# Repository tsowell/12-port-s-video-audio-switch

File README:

KiCad design, AVR code, and misc CAD files for a 12-port S-Video/audio
switch with VFD display, described in detail here:

https://blog.ldtlb.com/2021/03/25/12-port-s-video-audio-switch.html

The design in the KiCad files has multiple flaws.  Most importantly, the
terminating resistors for the luminance and chroma inputs were omitted, and the
+5VD voltage regualt can become quite hot without a large heatsink.  These are
explained in more detail in the post above.

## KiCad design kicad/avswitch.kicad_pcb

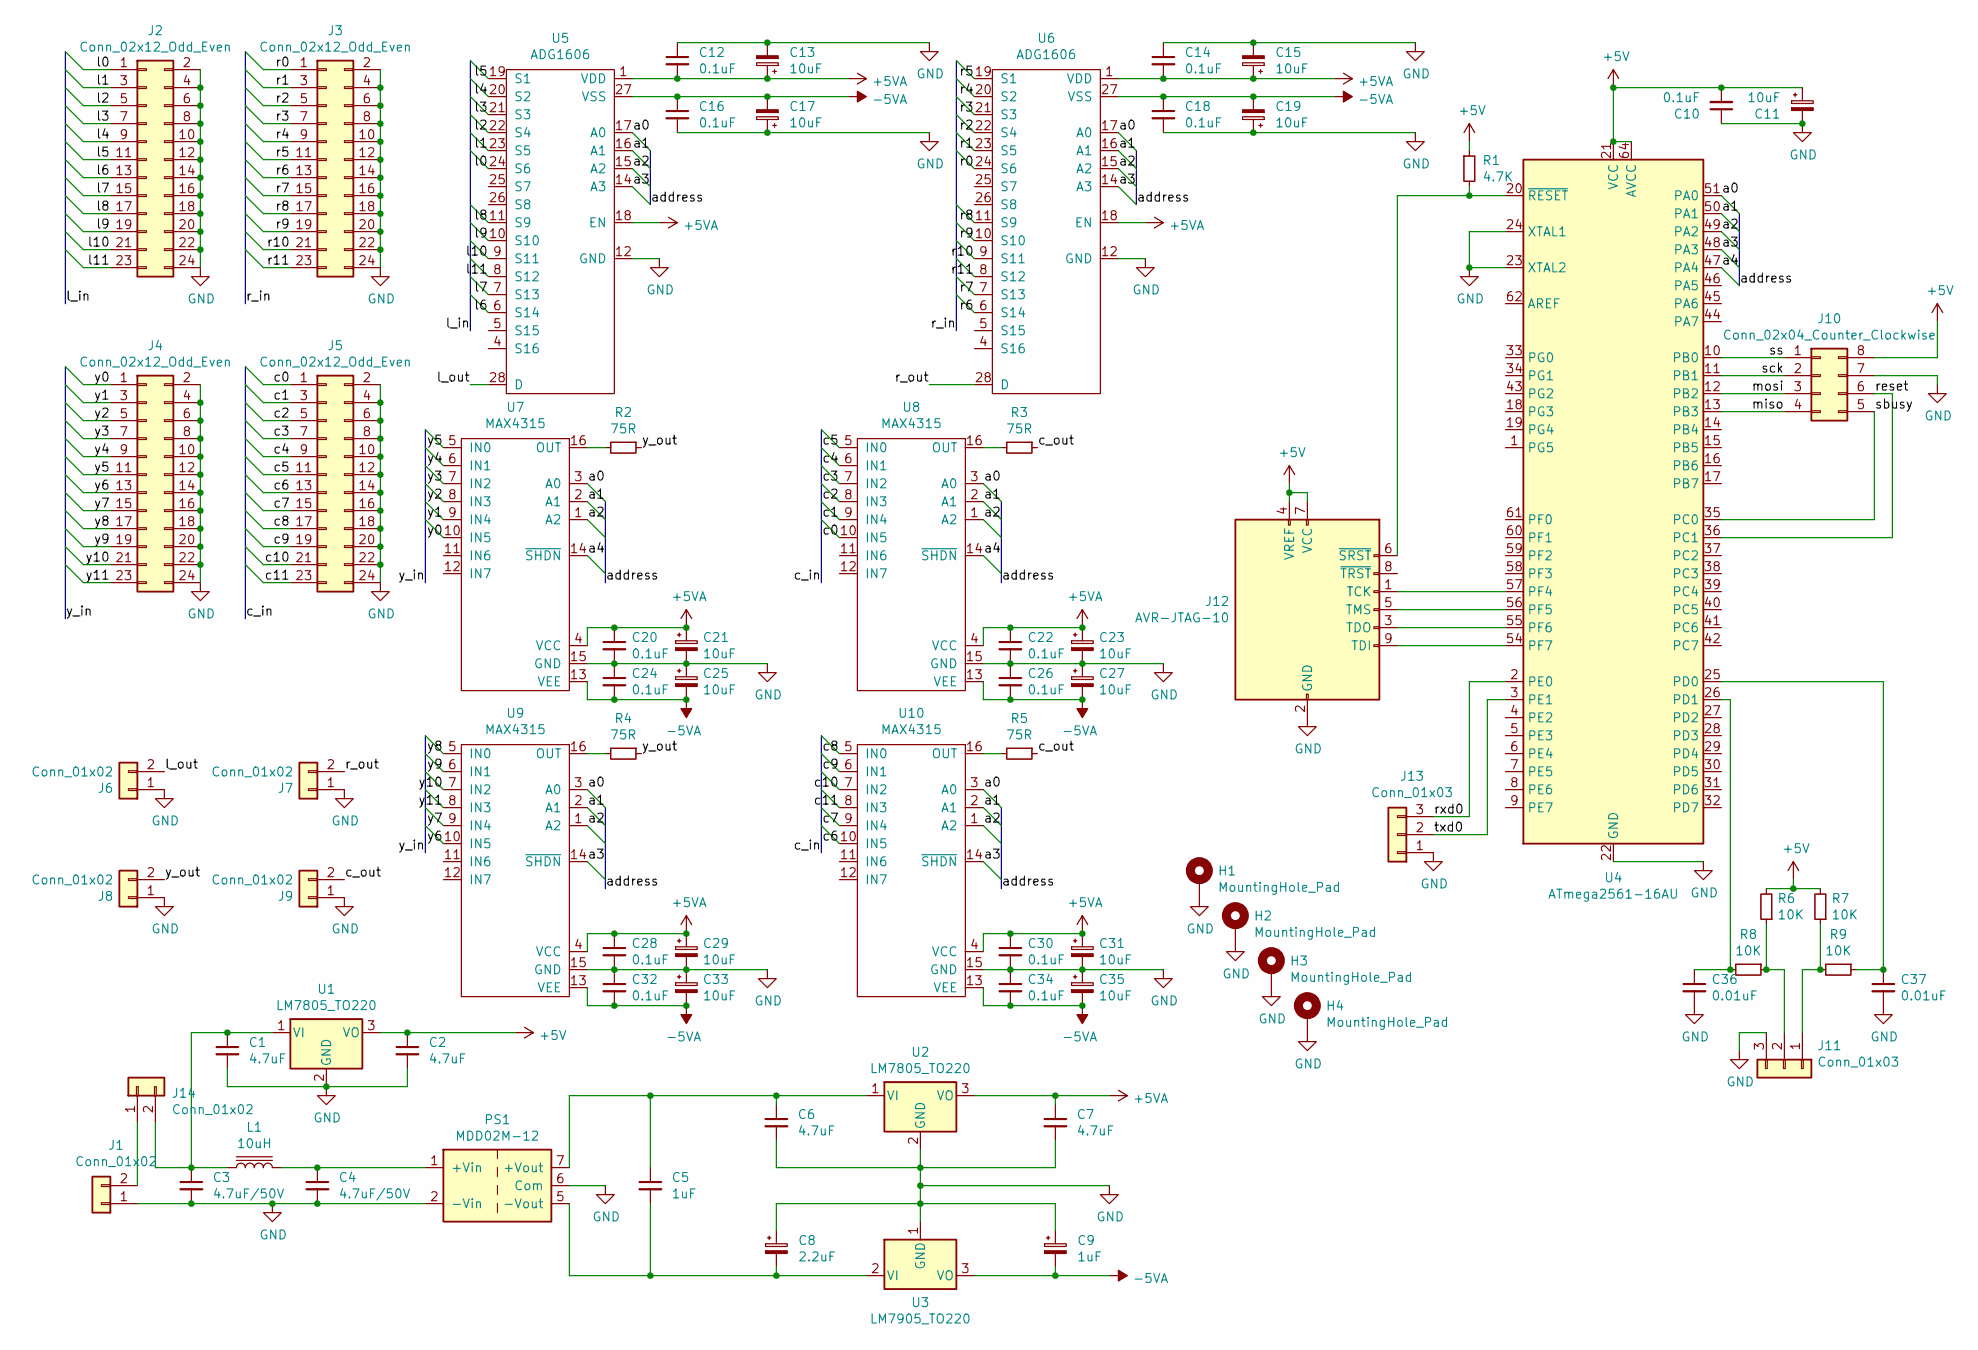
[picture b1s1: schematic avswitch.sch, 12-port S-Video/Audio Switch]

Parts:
C1, C2, C6, C7: 4.7uF; C_1206_3216Metric_Pad1.42x1.75mm_HandSolder; Part 399-3524-1-ND
C3, C4: 4.7uF/50V; C_1206_3216Metric_Pad1.42x1.75mm_HandSolder; Part 399-11685-1-ND
C5: 1uF; C_1206_3216Metric_Pad1.42x1.75mm_HandSolder; Part 399-1254-1-ND
C8: 2.2uF; CP_EIA-3216-18_Kemet-A_Pad1.58x1.35mm_HandSolder; Part 399-3691-1-ND
C9: 1uF; CP_EIA-3216-18_Kemet-A_Pad1.58x1.35mm_HandSolder; Part 399-3678-1-ND
C10, C12, C14, C16, C18, C20, C22, C24, C26, C28, C30, C32, C34: 0.1uF; C_1206_3216Metric_Pad1.42x1.75mm_HandSolder; Part 399-9305-1-ND
C11, C13, C15, C17, C19, C21, C23, C25, C27, C29, C31, C33, C35: 10uF; CP_Elec_4x5.4; Part 493-2173-1-ND
C36, C37: 0.01uF; C_1206_3216Metric_Pad1.42x1.75mm_HandSolder; Part 399-14645-1-ND
H1, H2, H3, H4: MountingHole_Pad; MountingHole_3.2mm_M3_Pad_Via
J1, J6, J7, J8, J9, J14: Conn_01x02; Molex_KK-254_AE-6410-02A_1x02_P2.54mm_Vertical; Part WM2700-ND
J2, J3, J4, J5: Conn_02x12_Odd_Even; PinHeader_2x12_P2.54mm_Vertical; Part ED10525-ND
J10: Conn_02x04_Counter_Clockwise; PinHeader_2x04_P2.54mm_Vertical; Part 732-5395-ND
J11: Conn_01x03; Molex_KK-254_AE-6410-03A_1x03_P2.54mm_Vertical; Part WM2701-ND
J12: AVR-JTAG-10; PinHeader_2x05_P1.27mm_Vertical; Part 1175-1627-ND
J13: Conn_01x03; PinHeader_1x03_P2.54mm_Vertical
L1: 10uH; L_1206_3216Metric_Pad1.42x1.75mm_HandSolder; Part 541-2607-6-ND
PS1: MDD02M-12; Part 1866-3383-ND
R1: 4.7K; R_1206_3216Metric_Pad1.42x1.75mm_HandSolder; Part 311-4.7KERCT-ND
R2, R3, R4, R5: 75R; R_1206_3216Metric_Pad1.42x1.75mm_HandSolder; Part 311-75ERCT-ND
R6, R7, R8, R9: 10K; R_1206_3216Metric_Pad1.42x1.75mm_HandSolder; Part 311-10KERCT-ND
U1, U2: LM7805_TO220; TO-220-3_Vertical; Part 296-47192-ND
U3: LM7905_TO220; TO-220-3_Vertical; Part LM7905CTNS/NOPB-ND
U4: ATmega2561-16AU; TQFP-64_14x14mm_P0.8mm; Part ATMEGA2561-16AURCT-ND
U5, U6: ADG1606; TSSOP-28_4.4x9.7mm_P0.65mm; Part ADG1606BRUZ-REEL7CT-ND
U7, U8, U9, U10: MAX4315; SOIC-16_3.9x9.9mm_P1.27mm

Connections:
+5V: C2.1, C10.2, C11.1, J10.8, J12.4 (VREF), J12.7 (VCC), R1.1, R6.2, R7.2, U1.3 (VO), U4.21 (VCC), U4.52 (VCC), U4.64 (AVCC)
+5VA: C7.1, C12.2, C13.1, C14.2, C15.1, C20.1, C21.1, C22.1, C23.1, C28.1, C29.1, C30.1, C31.1, U2.3 (VO), U5.1 (VDD), U5.18 (EN), U6.1 (VDD), U6.18 (EN), U7.4 (VCC), U8.4 (VCC), U9.4 (VCC), U10.4 (VCC)
-5VA: C9.2, C16.1, C17.2, C18.1, C19.2, C24.2, C25.2, C26.2, C27.2, C32.2, C33.2, C34.2, C35.2, U3.3 (VO), U5.27 (VSS), U6.27 (VSS), U7.13 (VEE), U8.13 (VEE), U9.13 (VEE), U10.13 (VEE)
/a0: U4.51 (PA0), U5.17 (A0), U6.17 (A0), U7.3 (A0), U8.3 (A0), U9.3 (A0), U10.3 (A0)
/a1: U4.50 (PA1), U5.16 (A1), U6.16 (A1), U7.2 (A1), U8.2 (A1), U9.2 (A1), U10.2 (A1)
/a2: U4.49 (PA2), U5.15 (A2), U6.15 (A2), U7.1 (A2), U8.1 (A2), U9.1 (A2), U10.1 (A2)
/a3: U4.48 (PA3), U5.14 (A3), U6.14 (A3), U9.14 (~SHDN), U10.14 (~SHDN)
/a4: U4.47 (PA4), U7.14 (~SHDN), U8.14 (~SHDN)
/c0: J5.1, U8.10 (IN5)
/c1: J5.3, U8.9 (IN4)
/c2: J5.5, U8.8 (IN3)
/c3: J5.7, U8.7 (IN2)
/c4: J5.9, U8.6 (IN1)
/c5: J5.11, U8.5 (IN0)
/c6: J5.13, U10.10 (IN5)
/c7: J5.15, U10.9 (IN4)
/c8: J5.17, U10.5 (IN0)
/c9: J5.19, U10.6 (IN1)
/c10: J5.21, U10.7 (IN2)
/c11: J5.23, U10.8 (IN3)
/c_out: J9.2, R3.1, R5.1
/l0: J2.1, U5.24 (S6)
/l1: J2.3, U5.23 (S5)
/l2: J2.5, U5.22 (S4)
/l3: J2.7, U5.21 (S3)
/l4: J2.9, U5.20 (S2)
/l5: J2.11, U5.19 (S1)
/l6: J2.13, U5.6 (S14)
/l7: J2.15, U5.7 (S13)
/l8: J2.17, U5.11 (S9)
/l9: J2.19, U5.10 (S10)
/l10: J2.21, U5.9 (S11)
/l11: J2.23, U5.8 (S12)
/l_out: J6.2, U5.28 (D)
/miso: J10.4, U4.13 (PB3)
/mosi: J10.3, U4.12 (PB2)
/r0: J3.1, U6.24 (S6)
/r1: J3.3, U6.23 (S5)
/r2: J3.5, U6.22 (S4)
/r3: J3.7, U6.21 (S3)
/r4: J3.9, U6.20 (S2)
/r5: J3.11, U6.19 (S1)
/r6: J3.13, U6.6 (S14)
/r7: J3.15, U6.7 (S13)
/r8: J3.17, U6.11 (S9)
/r9: J3.19, U6.10 (S10)
/r10: J3.21, U6.9 (S11)
/r11: J3.23, U6.8 (S12)
/r_out: J7.2, U6.28 (D)
/reset: J10.6, U4.36 (PC1)
/rxd0: J13.3, U4.2 (PE0)
/sbusy: J10.5, U4.35 (PC0)
/sck: J10.2, U4.11 (PB1)
/ss: J10.1, U4.10 (PB0)
/txd0: J13.2, U4.3 (PE1)
/y0: J4.1, U7.10 (IN5)
/y1: J4.3, U7.9 (IN4)
/y2: J4.5, U7.8 (IN3)
/y3: J4.7, U7.7 (IN2)
/y4: J4.9, U7.6 (IN1)
/y5: J4.11, U7.5 (IN0)
/y6: J4.13, U9.10 (IN5)
/y7: J4.15, U9.9 (IN4)
/y8: J4.17, U9.5 (IN0)
/y9: J4.19, U9.6 (IN1)
/y10: J4.21, U9.7 (IN2)
/y11: J4.23, U9.8 (IN3)
/y_out: J8.2, R2.1, R4.1
GND: C1.2, C2.2, C3.2, C4.2, C6.2, C7.2, C8.1, C9.1, C10.1, C11.2, C12.1, C13.2, C14.1, C15.2, C16.2, C17.1, C18.2, C19.1, C20.2, C21.2, C22.2, C23.2, C24.1, C25.1, C26.1, C27.1, C28.2, C29.2, C30.2, C31.2, C32.1, C33.1, C34.1, C35.1, C36.2, C37.2, H1.1, H2.1, H3.1, H4.1, J1.1, J2.2, J2.4, J2.6, J2.8, J2.10, J2.12, J2.14, J2.16, J2.18, J2.20, J2.22, J2.24, J3.2, J3.4, J3.6, J3.8, J3.10, J3.12, J3.14, J3.16, J3.18, J3.20, J3.22, J3.24, J4.2, J4.4, J4.6, J4.8, J4.10, J4.12, J4.14, J4.16, J4.18, J4.20, J4.22, J4.24, J5.2, J5.4, J5.6, J5.8, J5.10, J5.12, J5.14, J5.16, J5.18, J5.20, J5.22, J5.24, J6.1, J7.1, J8.1, J9.1, J10.7, J11.3, J12.2 (GND), J12.10 (GND), J13.1, PS1.2 (-Vin), PS1.6 (Com), U1.2 (GND), U2.2 (GND), U3.1 (GND), U4.22 (GND), U4.23 (XTAL2), U4.24 (XTAL1), U4.53 (GND), U4.63 (GND), U5.12 (GND), U6.12 (GND), U7.15 (GND), U8.15 (GND), U9.15 (GND), U10.15 (GND)
unnamed: C1.1, C3.1, J14.2, L1.1, U1.1 (VI)
unnamed: C4.1, L1.2, PS1.1 (+Vin)
unnamed: C5.1, C6.1, PS1.7 (+Vout), U2.1 (VI)
unnamed: C5.2, C8.2, PS1.5 (-Vout), U3.2 (VI)
unnamed: C36.1, R8.2, U4.26 (PD1)
unnamed: C37.1, R9.1, U4.25 (PD0)
unnamed: J1.2, J14.1
unnamed: J11.1, R7.1, R9.2
unnamed: J11.2, R6.1, R8.1
unnamed: J12.1 (TCK), U4.57 (PF4)
unnamed: J12.3 (TDO), U4.55 (PF6)
unnamed: J12.5 (TMS), U4.56 (PF5)
unnamed: J12.6 (~SRST), R1.2, U4.20 (~RESET)
unnamed: J12.9 (TDI), U4.54 (PF7)
unnamed: R2.2, U7.16 (OUT)
unnamed: R3.2, U8.16 (OUT)
unnamed: R4.2, U9.16 (OUT)
unnamed: R5.2, U10.16 (OUT)

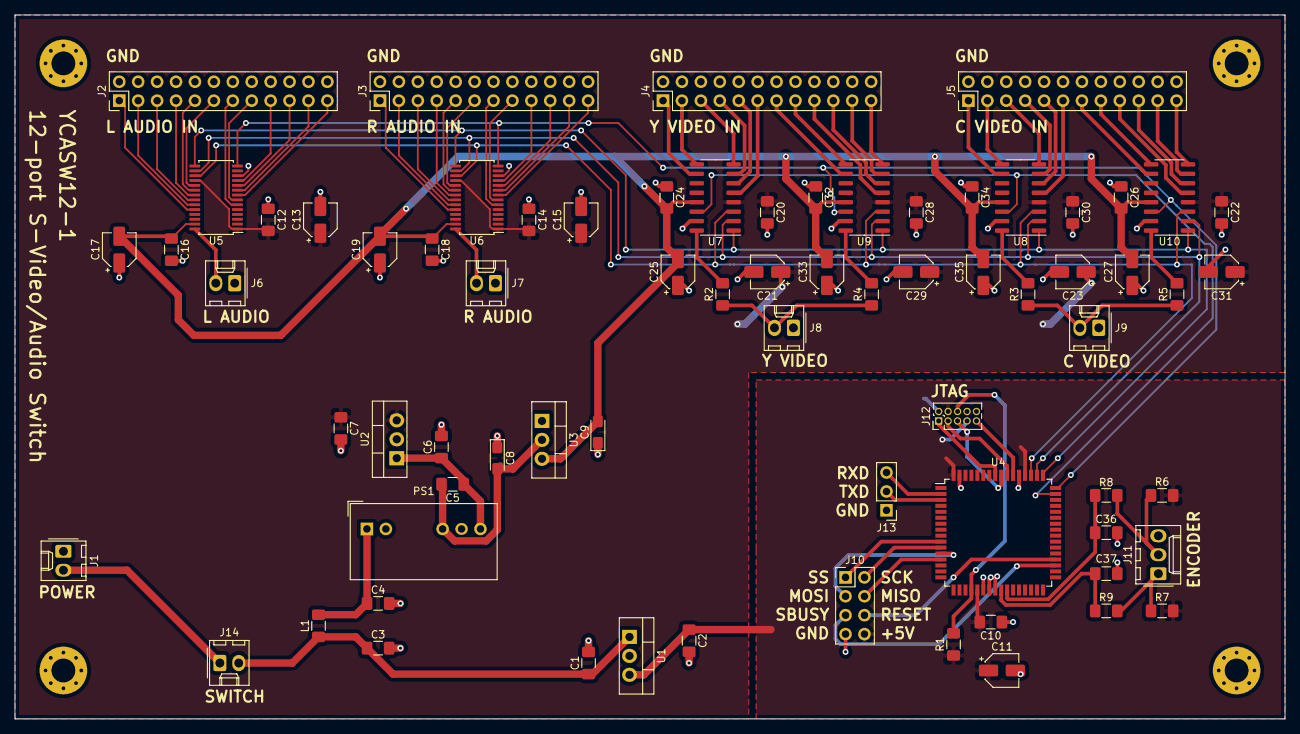
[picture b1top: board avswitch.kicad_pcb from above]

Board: 2 copper layers, 170.5 x 94.5 mm, 76 parts (0 on the bottom side), 87 nets.

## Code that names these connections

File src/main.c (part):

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spi_init(void)
{
	/* Set /SS, SCK, and MOSI to output. */
	DDRB |= (1 << PB2) | (1 << PB1) | (1 << PB0);
	/* The AVR SPI system will not drive /SS when it is
	 * set as an output, so set it here in order to select
	 * the device. */
	PORTB &= ~(1 << PB0);

	/* Enable SPI master mode, double speed. */
	SPCR = (1 << SPE) | (1 << MSTR) | (1 << SPI2X);
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vfd_wait_busy(void)
{
	/* Poll the VFD's busy pin. */
	while (!(PINC & (1 << PC0))) {
	}
}

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vfd_wait_notbusy(void)
{
	/* Poll the VFD's busy pin. */
	while ((PINC & (1 << PC0))) {
	}
}

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vfd_init(void)
{
	/* Set the VFD reset pin to output. */
	DDRC = (1 << PC1);
	/* Reset VFD with a falling edge on the reset line,
	 * followed by a rising edge 2 ms later.*/
	PORTC = (1 << PC1); /* Reset high. */
	spi_init();
	PORTC = 0x00; /* Reset low. */
	_delay_ms(2);
	PORTC = (1 << PC1); /* Reset high. */

	/* Wait for the VFD to initialize. */
	vfd_wait_busy();
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	 * time the encoder value changes to configure the interrupt triggers
	 * and directions. */

	/* Configure PD0 and PD1 as inputs */
	DDRD &= ~(1 << PD0);
	DDRD &= ~(1 << PD1);

	/* Enable the pull-up resistors */
	PORTD |= (1 << PD0) | (1 << PD1);

	/* PD1:PD0 goes 00 => 01 => 11 => 10 => 00 from left to right, so... */

	/* PP  Configure interrupts based on current encoder value.
	 * DD  enc_dir_1 and enc_dir_0 are passed from the ISRs to
	 * 10  encoder_interrupt().
	 * --
	 * 00: PD1 rise means left, PD0 rise means right
	 * 01: PD0 fall means left, PD1 rise means right
	 * 11: PD1 fall means left, PD0 fall means right
	 * 10: PD0 rise means left, PD1 fall means right
	 * */
	uint8_t d = PIND & 0x03;
        if (d == 0x00) {
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
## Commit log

2021-03-31 Add MIT license
